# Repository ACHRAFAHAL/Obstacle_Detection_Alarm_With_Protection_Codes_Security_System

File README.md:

# Obstacle Detection Alarm Secured by Protection Codes

## Description

This project outlines the design and implementation of an obstacle detection system that triggers a frequency-modulated audible alarm upon detecting a disrupted red LASER beam. The alarm's deactivation is secured through a precise sequence of three hexadecimal codes, complemented by a rescue code for single errors and a super-code for multiple erroneous entries. This system is ideally suited for various security, surveillance, or access control applications where the detection of unauthorized presence or intrusion is paramount.

## Table of Contents

- [Features](#features)
- [Required Hardware](#required-hardware)
- [Schematics](#schematics)
- [Installation](#installation)
- [Usage](#usage)
- [Contributing](#contributing)

## Features

- **Optical Detection**: The system employs a red LASER emitter and a pair of BPX81 phototransistors for precise obstacle detection. During initial testing phases, a push-button can substitute the optical detection for functional verification. The detection logic utilizes a 74LS32 OR gate, which triggers the alarm as soon as either sensor detects a beam interruption. Visual feedback for sensor activation is provided by a green LED. A LM311 comparator then converts the analog output of the OR gate into a binary signal compatible with the microcontroller.

- **Audible Alarm****: The alarm generates a distinctive two-tone binary modulated sound, alternating between 2500 Hz and 5000 Hz every 0.5 seconds. The core of the sound generation is the XR2206 integrated circuit, configured as a voltage-controlled oscillator (VCO), capable of generating a clean sinusoidal signal. The signal processing chain involves integrating the microcontroller's square wave output into a triangular signal (0-3V) suitable for the XR2206's VCO input, followed by amplification via a push-pull stage to drive the KSSG1708 loudspeaker.

- **Security** Sequence: Alarm deactivation is protected by a precise three-code hexadecimal sequence (Code 1, Code 2, Code 3). In case of an incorrect entry, a "DEFAUT" rescue code (Code 4) can be used for a restricted unlock. For multiple errors, an "ERREUR" super-code (Code 5) is required to fully reset the system procedure. This sequential logic is managed by a state machine implemented in the microcontroller's firmware.

- **Visual Indicators**: The system provides clear visual feedback through three LEDs: a green LED indicates a correct procedure in progress (States 1, 2, and 3). An orange LED signifies the "DEFAUT" state, while a red LED illuminates for the "ERREUR" state. These LEDs are directly driven by the microcontroller.

- **Microcontroller**: The STM32L476RG microcontroller (Nucleo-L476RG development board) serves as the central processing unit, handling the sequential and combinational logic for code verification, error state management (DEFAUT, ERREUR), and memory for predefined codes. It interfaces with a rotary encoder for user input  and an OLED-SSD1306 display for detailed system status and code entry prompts. The microcontroller's internal peripherals, such as timers (TIM2 for encoder, TIM4 for PWM siren ) and external interrupts (EXTI for encoder button ), ensure real-time and reactive system operation.

## Required Hardware

- **LASER emitter**: ADL-65075TL (not explicitly mentioned as a specific component but implied by "red LASER beam" ).
  
- **Phototransistor**: BPX81.
  
- **Operational amplifiers**: TL082  (used in the audio signal chain ).
  
- **Comparator**: LM311.
  
- **Logic Gate**: 74LS32 (OR gate).
  
- **Timer**: While a NE555 is listed in the example, the STM32L476RG's internal timers (TIM2, TIM4) are primarily used for encoder interface  and PWM siren generation  in the project.
  
- **Function generator**: XR2206.
  
- **Mini speaker**: KSSG1708.
  
- **DC-DC Converter**:
IA1215S (for ±15V symmetric power to the audio circuit).
Wurth 173010542 (12V to 5V conversion for the control part).

- **LDO Regulator**: AZ1117CH2-3.3TRG1 (SOT-223 package, for 5V to 3.3V regulation).

- **Development board**: STM32L476RG (Nucleo-L476RG).

- **LEDs**:
Red LEDs (0603 SMD): Quantity: 4 (for power control  and error indication ).
Yellow LED (0603 SMD): Quantity: 1 (for DEFAUT state indication).
Green LED (0603 SMD): Quantity: 1 (for correct procedure indication).

- **Resistors**: Various values (e.g., 220Ω, 400Ω, 800Ω, 1kΩ, 1.6kΩ, 5.1kΩ, 820Ω, 10kΩ, 15kΩ, 3.3kΩ ).
  
- **User inputs**: Rotary encoder (Incrémental MEC (482016514001)) with integrated push-button.

- **Display**: OLED-SSD1306 (I2C interfaced, SBC-OLED01 model).

- **Capacitors**: A range of ceramic (10nF, 100nF ) and electrolytic (1µF, 10µF, 22µF, 47µF, 100µF ) capacitors for filtering, decoupling, and signal coupling.

- **Connectors**: JST connectors (Conn_01x02, Conn_01x03, Conn_01x04 ) for inter-module connections and power input.

- **Protection Diodes**: ESD diodes (WE 82402374) for protecting I2C and encoder lines from electrostatic discharge.

- **Potentiometers**: 20KΩ, 50KΩ, 500Ω  for fine-tuning.

## Schematics

1. **System General Diagram**  
   
   A comprehensive block diagram illustrating the interconnections between the main functional modules: Supply (providing +12V, +5V, +3.3V), NUCLEO-L476RG microcontroller, Rotary Encoder, and Input/Output signals (VALID_ALARM, SIG_ALARM, INPUT, INPUT_Supply). It also shows the I2C connection to the OLED-SSD1306 display  and the mounting holes for the PCB.
   
3. **Sensor Model**  
   
   This schematic details the obstacle detection unit. It includes two BPX81 phototransistors (Q1, Q2)  that detect the interruption of the LASER beam. Their outputs feed into a 74LS32 OR gate (U1), which activates when either beam is broken. A verification LED (D3, GREEN_LED)  provides visual confirmation of sensor activation. The signal is then passed to an LM311 comparator (U2), which compares the OR gate's output to a 2.5V reference voltage, producing a binary signal for the microcontroller. This section also includes power supply filtering and visual indicators using NPN (2N1711) and PNP (2N2905) transistors.
   
5. **Audio Signal Chain**  
   
   This diagram illustrates the steps involved in generating and amplifying the alarm sound. The process begins with a square wave signal (0 to 3.3V) from the microcontroller (STM32). This signal is then integrated by an operational amplifier (U1A) to transform it into a triangular wave centered at 0V (±1.65V). A second operational amplifier (U1B), configured as a non-inverting amplifier, shifts and scales this signal to a 0-3V range, suitable for the XR2206's VCO input. The XR2206 (U2) then generates the frequency-modulated sinusoidal signal (2500 Hz / 5000 Hz). Finally, this signal is amplified by a symmetric push-pull stage using 2N1711 (Q1) and 2N2905 (Q2) transistors  to drive the KSSG1708 loudspeaker (LS1). The audio circuit is powered by a ±15V symmetric supply generated by an IA1215S DC-DC converter (PS1) from a 12V input.
   
7. **Unlock Sequence**  
   
   This state graph (Figure 1.1) visually represents the precise sequential logic for alarm deactivation. Starting from the "ALARME INACTIVE" (Etat 0) state, an active sensor transitions the system to "ALARME ACTIVE" (Etat 1). The user must then enter three correct codes sequentially (Code 1, Code 2, Code 3), moving through Etat 1, Etat 2, and Etat 3. If any code is incorrect, the system branches to a "DEFAUT" state (Etat 4), requiring Code 4. If Code 4 is incorrect, or multiple errors occur, it transitions to an "ERREUR" state (Etat 5), requiring Code 5 to reset the system. A successful sequence at Etat 3 returns the system to "ALARME INACTIVE" (Etat 0).

## Installation

**PCB Fabrication**: Generate Gerber files from the KiCad projects for each of the three main parts: Detection, Control, and Actuator. These files are then sent to a PCB manufacturer.

**Component Soldering**: Upon receiving the engraved PCBs, manually solder all through-hole components. Special attention should be paid to the spacing and quality of solder joints to prevent issues like short-circuits, as encountered during initial testing.

**Power Supply Integration**: For the Control PCB, integrate the J401 connector for the 12V input, the Wurth 173010542 DC-DC converter (U401) for 12V to 5V conversion, and the AZ1117CH2-3.3TRG1 LDO regulator (U402) for 5V to 3.3V regulation. Visual control LEDs (D401, D402, D403) should be verified for proper operation.

**Microcontroller Setup**: Carefully mount the Nucleo-L476RG board onto the designated footprint on the Control PCB.
Interconnections: Connect the Detection module to the Control module via J1 and J3 connectors. Ensure proper signal connections for INPUT (laser detection)  and INPUT_Supply. Connect the Control module to the Actuator module via the J2 connector, ensuring correct routing for VALID_ALARM (alarm activation signal)  and SIG_ALARM (power supply to the output circuit).

**Firmware**: Program the STM32L476RG microcontroller with the project firmware. The software is designed with a modular architecture, leveraging the microcontroller's internal peripherals such as timers (TIM2 for encoder, TIM4 for PWM siren ), external interrupts (EXTI for encoder button press ), I2C for OLED communication, and GPIOs for LED control. This ensures efficient and responsive operation.

## Usage
**System Activation**: The alarm system is initialized in an "ALARM INACTIVE" (Etat 0) state, as shown on the OLED display.
Obstacle Detection: When an obstacle interrupts the LASER beam, the phototransistors detect the change, triggering the 74LS32 OR gate  and the LM311 comparator. This sends a logical front signal to the STM32's INPUT pin, transitioning the system to the "ALARM ACTIVE" state (Etat 1). The audible alarm will simultaneously be triggered.

**Alarm Deactivation**: To disarm the alarm, the user must enter a sequence of three correct hexadecimal codes (Code 1, Code 2, Code 3) using the rotary encoder. 
Code Entry: Rotate the encoder to select a character (0 to F)  and press the integrated push-button to validate each character. The OLED display will guide the user by showing prompts like "CODE 1:X", "CODE D:X", or "CODE E:X".

**Correct Sequence**: Successful entry of Code 1, Code 2, and Code 3 (transitioning through Etat 1, Etat 2, and Etat 3)  will deactivate the alarm, and the system will revert to the "ALARM OFF" state (Etat 0). The green LED will illuminate during the correct procedure.

Incorrect Entry (DEFAUT State): If a code is entered incorrectly, the system may transition to the "DEFAUT" state (Etat 4), requiring the user to enter a specific rescue code (Code 4). The orange LED will indicate this state.

Multiple Errors (ERREUR State): In cases of multiple incorrect entries or an incorrect rescue code, the system will enter the "ERREUR" state (Etat 5), demanding the entry of a super-code (Code 5)  to reset the entire procedure and return to Etat 0. The red LED will blink to signify this critical error state.

**Visual Feedback**: The OLED display provides real-time information on the system's status and the progress of code entry. The three colored LEDs (Green, Orange, Red) offer immediate visual cues regarding the system's current state and the validity of code entries.

## contributing

<br>

<table align="center">
  <tr>
    <td align="center">
      <br />
      <sub><b>Ahal Achraf</b></sub><br />
      <small>Control Part</small><br />
      <a href="https://github.com/ACHRAFAHAL">GitHub</a>
    </td>
  </tr>
  <tr>
    <td align="center">
      <br />
      <sub><b>Hussain Ali</b></sub><br />
      <small>Control Part</small><br />
      <a href="https://github.com/H-Ali-92">GitHub</a>
   </td>
  </tr>
</table>
<br>

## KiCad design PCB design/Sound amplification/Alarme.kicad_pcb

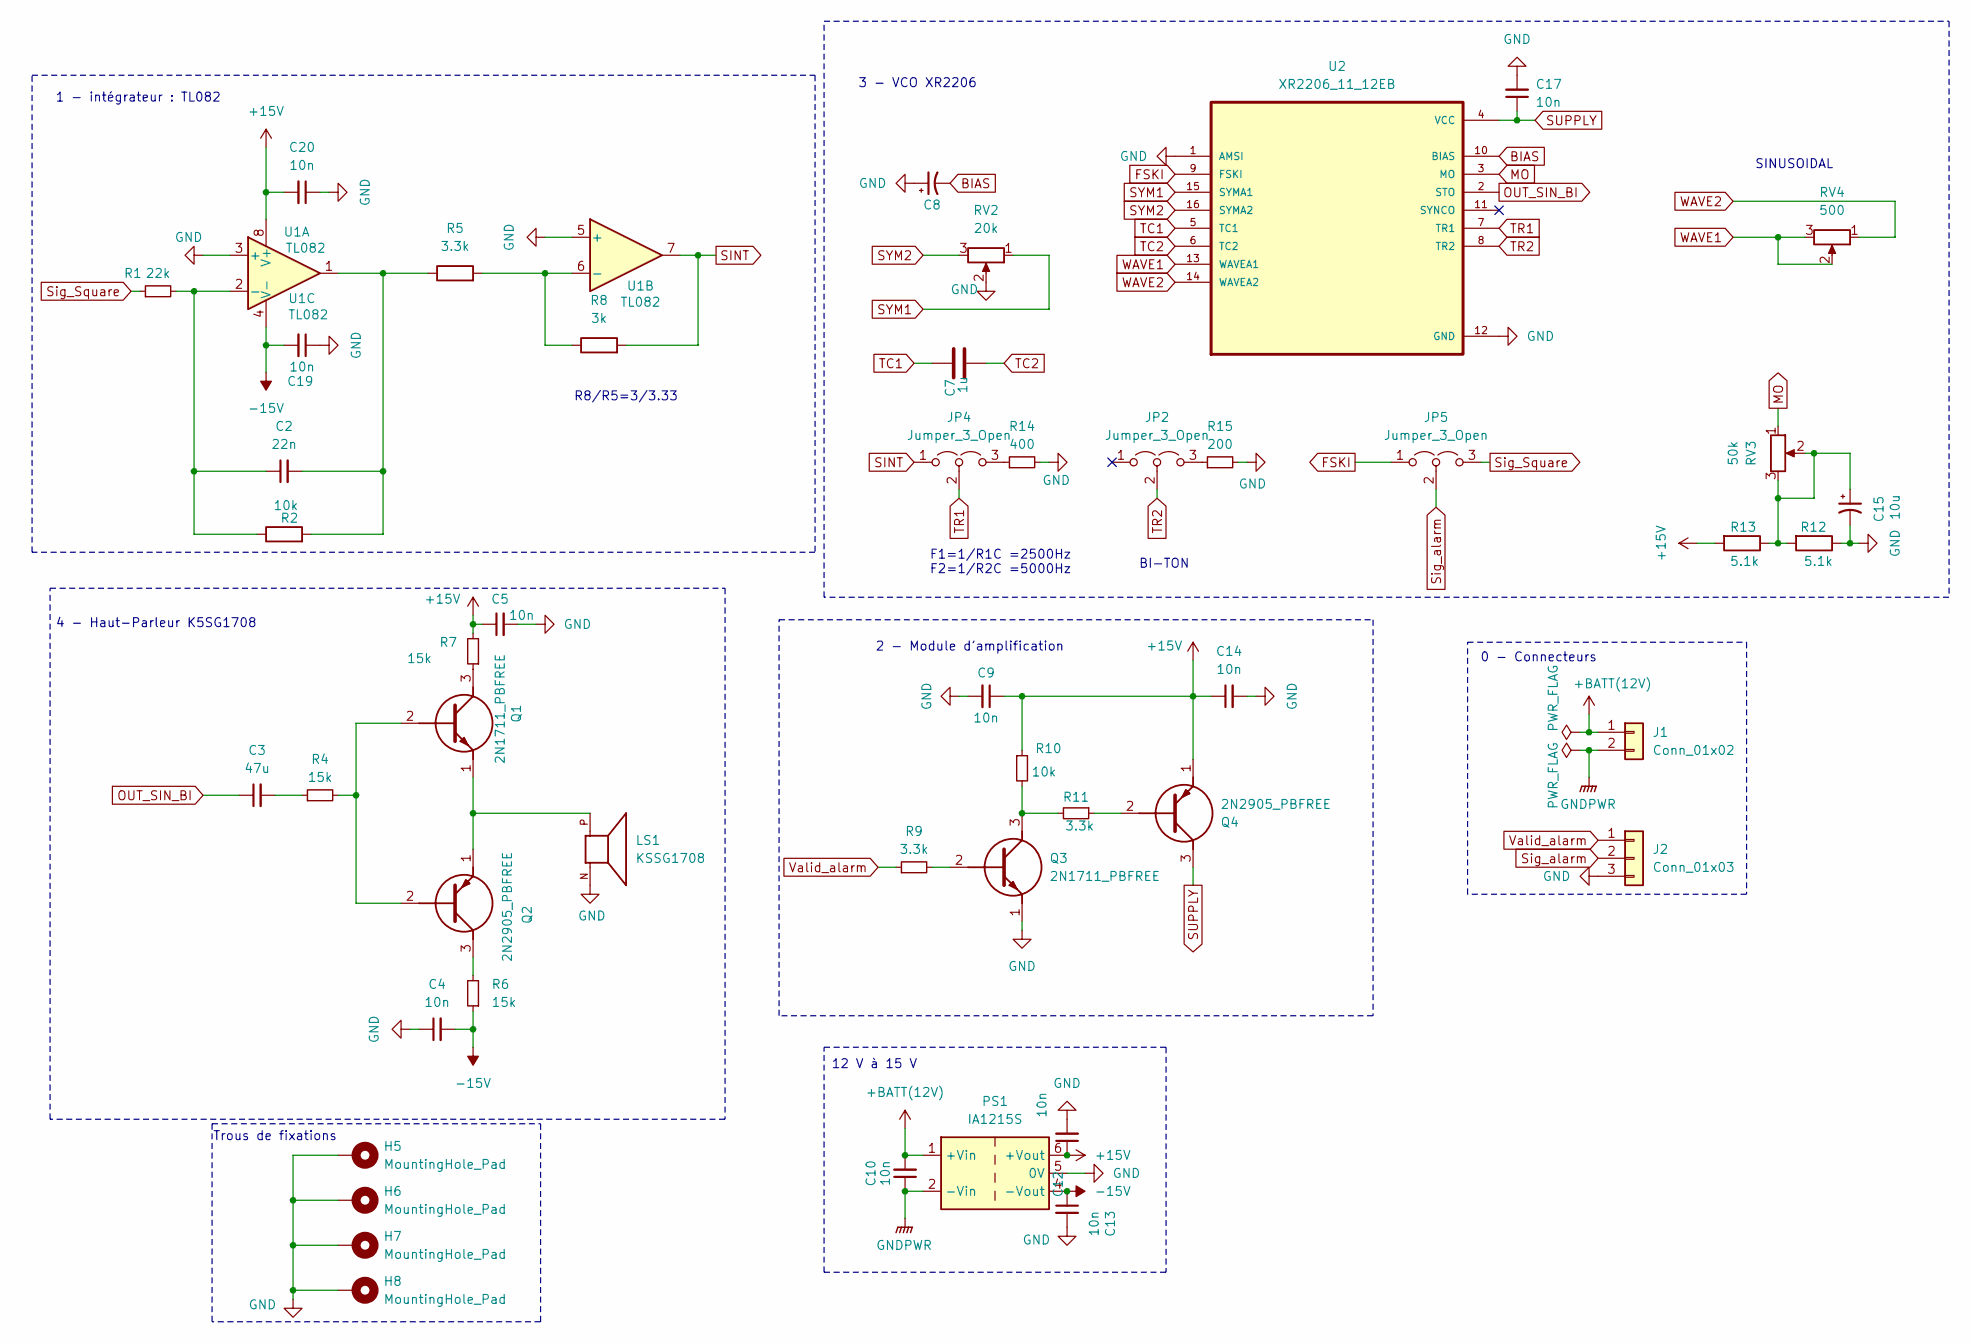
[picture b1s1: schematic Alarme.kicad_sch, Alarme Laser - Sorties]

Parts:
C2: 22n; CP_Radial_Tantal_D4.5mm_P5.00mm
C3: 47u; CP_Radial_Tantal_D4.5mm_P5.00mm
C4, C5, C8, C9, C10, C12, C13, C14, C17, C19, C20: 10n; CP_Radial_Tantal_D4.5mm_P5.00mm
C7: 1u; CP_Radial_Tantal_D4.5mm_P5.00mm
C15: 10u; CP_Radial_Tantal_D4.5mm_P5.00mm
H5, H6, H7, H8: MountingHole_Pad; MountingHole_3.2mm_M3_DIN965_Pad
J1: Conn_01x02; JST_XH_B2B-XH-A_1x02_P2.50mm_Vertical
J2: Conn_01x03; JST_XH_B3B-XH-A_1x03_P2.50mm_Vertical
JP2, JP4, JP5: Jumper_3_Open; PinHeader_1x03_P2.54mm_Vertical
LS1: KSSG1708; SPKR_KSSG1708; PARTREV 1.1
PS1: IA1215S; Converter_DCDC_XP_POWER-IAxxxxS_THT
Q1, Q3: 2N1711_PBFREE; TO39; Mouser Part Number 610-2N1711
Q2, Q4: 2N2905_PBFREE; TO39; Mouser Part Number 610-2N2905
R1: 22k; R_Axial_DIN0204_L3.6mm_D1.6mm_P2.54mm_Vertical
R2, R10: 10k; R_Axial_DIN0204_L3.6mm_D1.6mm_P2.54mm_Vertical
R4, R6, R7: 15k; R_Axial_DIN0204_L3.6mm_D1.6mm_P2.54mm_Vertical
R5, R9, R11: 3.3k; R_Axial_DIN0204_L3.6mm_D1.6mm_P2.54mm_Vertical
R8: 3k; R_Axial_DIN0204_L3.6mm_D1.6mm_P2.54mm_Vertical
R12, R13: 5.1k; R_Axial_DIN0204_L3.6mm_D1.6mm_P2.54mm_Vertical
R14: 400; R_Axial_DIN0204_L3.6mm_D1.6mm_P2.54mm_Vertical
R15: 200; R_Axial_DIN0204_L3.6mm_D1.6mm_P2.54mm_Vertical
RV2: 20k; Potentiometer_ACP_CA9-H5_Horizontal
RV3: 50k; Potentiometer_ACP_CA9-H5_Horizontal
RV4: 500; Potentiometer_ACP_CA9-H5_Horizontal
U1: TL082; DIP794W53P254L959H508Q8N
U2: XR2206_11_12EB; DIP-16_W7.62mm_LongPads; PART_REV 1.03; DIGI-KEY_PART_NUMBER 1016-1428-ND

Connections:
+15V: C5.1, C9.1, C12.1, C14.1, C20.2, PS1.6 (+Vout), Q4.1 (E), R7.2, R10.1, R13.2, U1.8 (V+)
+BATT(12V): C10.2, J1.1, PS1.1 (+Vin)
-15V: C4.2, C13.1, C19.2, PS1.4 (-Vout), R6.1, U1.4 (V-)
BIAS: C8.2, U2.10 (BIAS)
FSKI: JP5.1 (A), U2.9 (FSKI)
GND: C4.1, C5.2, C8.1, C9.2, C12.2, C13.2, C14.2, C15.2, C17.2, C19.1, C20.1, H5.1, H6.1, H7.1, H8.1, J2.3, LS1.N, PS1.5 (0V), Q3.1 (E), R12.1, R14.2, R15.2, RV2.2, U1.3 (+), U1.5 (+), U2.1 (AMSI), U2.12 (GND)
GNDPWR: C10.1, J1.2, PS1.2 (-Vin)
MO: RV3.1, U2.3 (MO)
unnamed: C2.2, R2.2, R5.1, U1.1
unnamed: C3.2, R4.1
unnamed: C15.1, R12.2, R13.1, RV3.2, RV3.3
unnamed: JP2.3 (B), R15.1
unnamed: JP4.3 (B), R14.1
unnamed: Q1.2 (B), Q2.2 (B), R4.2
unnamed: Q1.3 (C), R7.1
unnamed: LS1.P, Q1.1 (E), Q2.1 (E)
unnamed: Q2.3 (C), R6.2
unnamed: Q3.2 (B), R9.2
unnamed: Q3.3 (C), R10.2, R11.2
unnamed: Q4.2 (B), R11.1
unnamed: C2.1, R1.2, R2.1, U1.2 (-)
unnamed: R5.2, R8.1, U1.6 (-)
OUT_SIN_BI: C3.1, U2.2 (STO)
SINT: JP4.1 (A), R8.2, U1.7
SUPPLY: C17.1, Q4.3 (C), U2.4 (VCC)
SYM1: RV2.1, U2.15 (SYMA1)
SYM2: RV2.3, U2.16 (SYMA2)
Sig_Square: JP5.3 (B), R1.1
Sig_alarm: J2.2, JP5.2 (C)
TC1: C7.1, U2.5 (TC1)
TC2: C7.2, U2.6 (TC2)
TR1: JP4.2 (C), U2.7 (TR1)
TR2: JP2.2 (C), U2.8 (TR2)
Valid_alarm: J2.1, R9.1
WAVE1: RV4.2, RV4.3, U2.13 (WAVEA1)
WAVE2: RV4.1, U2.14 (WAVEA2)

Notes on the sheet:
BI-TON
R8/R5=3/3.33
F1=1/R1C =2500Hz F2=1/R2C =5000Hz
SINUSOIDAL
3 - VCO XR2206
1 - intégrateur : TL082
0 - Connecteurs
Trous de fixations
4 - Haut-Parleur K5SG1708
2 - Module d'amplification
12 V à 15 V

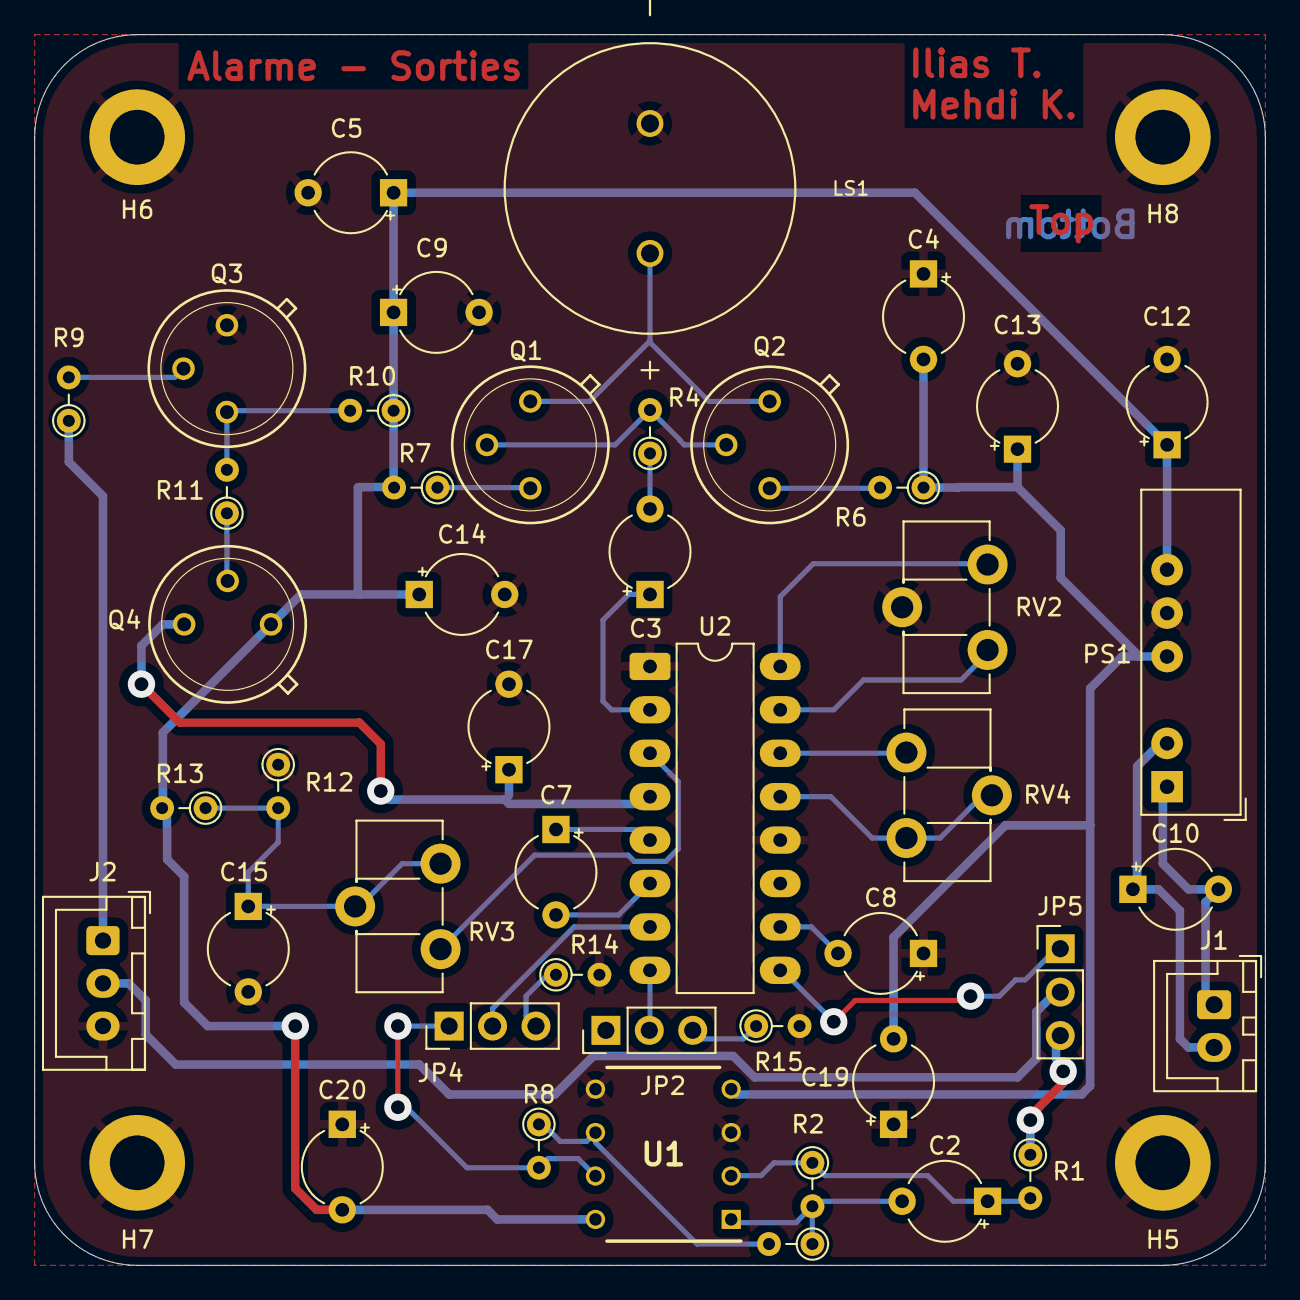
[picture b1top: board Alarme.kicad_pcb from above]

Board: 2 copper layers, 72.0 x 72.0 mm, 49 parts (0 on the bottom side), 36 nets.

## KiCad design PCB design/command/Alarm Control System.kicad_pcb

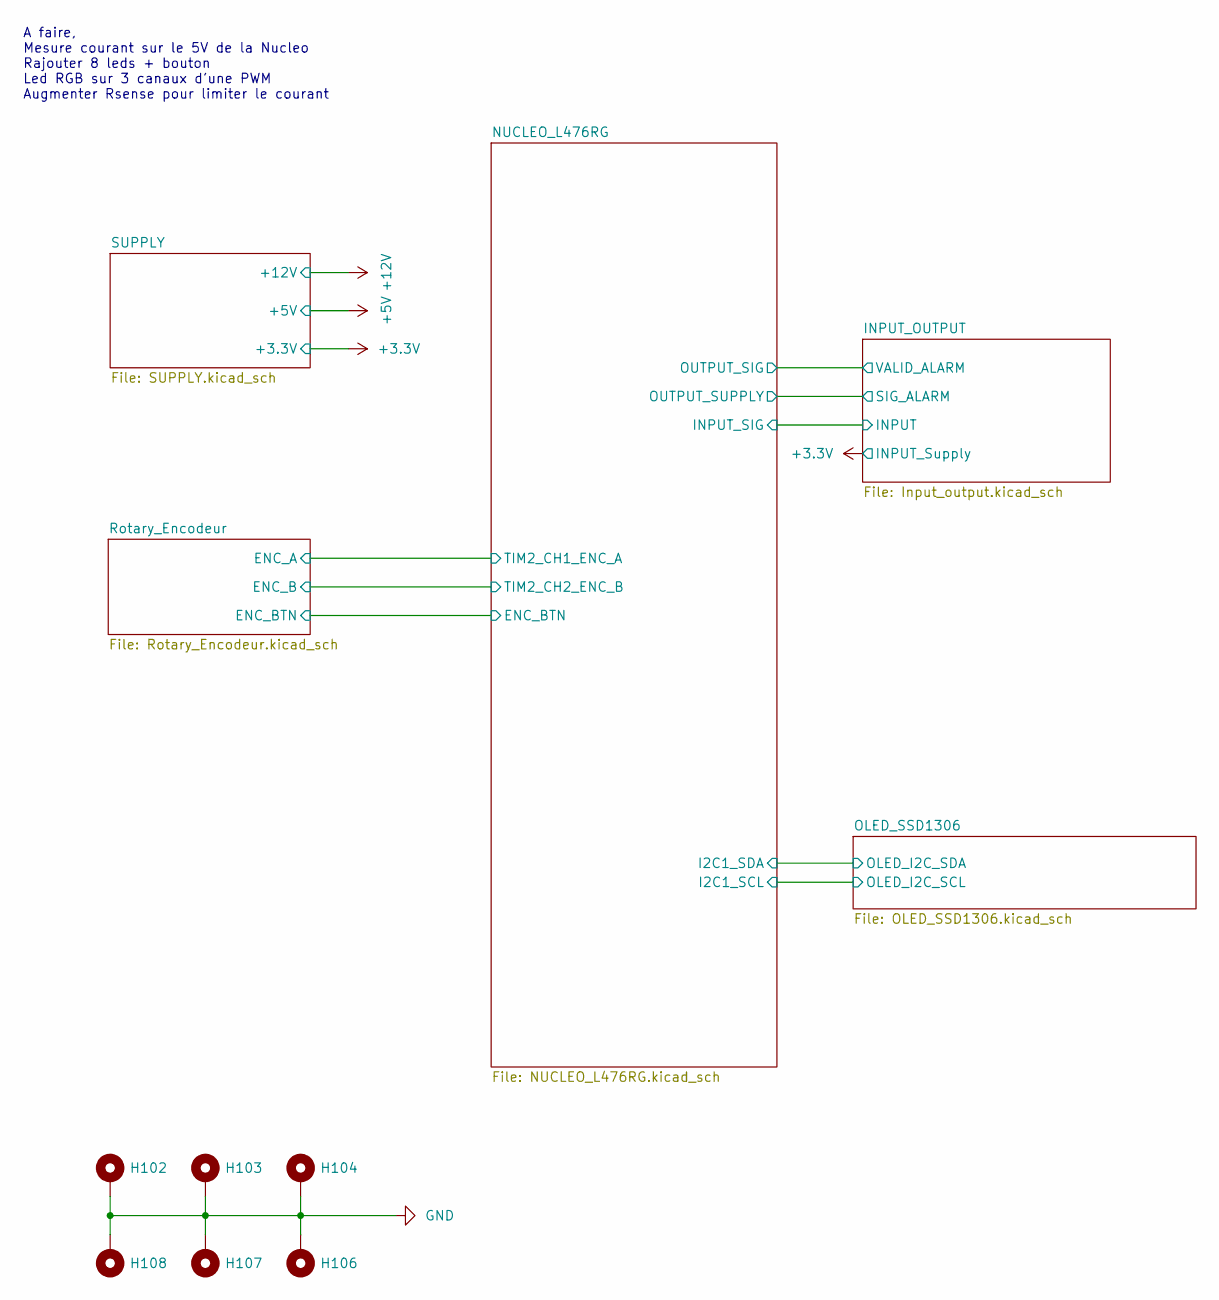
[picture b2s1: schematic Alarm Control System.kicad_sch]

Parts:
H102, H103, H104, H106, H107, H108: MountingHole_Pad; MountingHole_3.2mm_M3_Pad

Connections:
GND: H102.1, H103.1, H104.1, H106.1, H107.1, H108.1; also elsewhere on the board

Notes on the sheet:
A faire, Mesure courant sur le 5V de la Nucleo Rajouter 8 leds + bouton Led RGB sur 3 canaux d'une PWM Augmenter Rsense pour limiter le courant

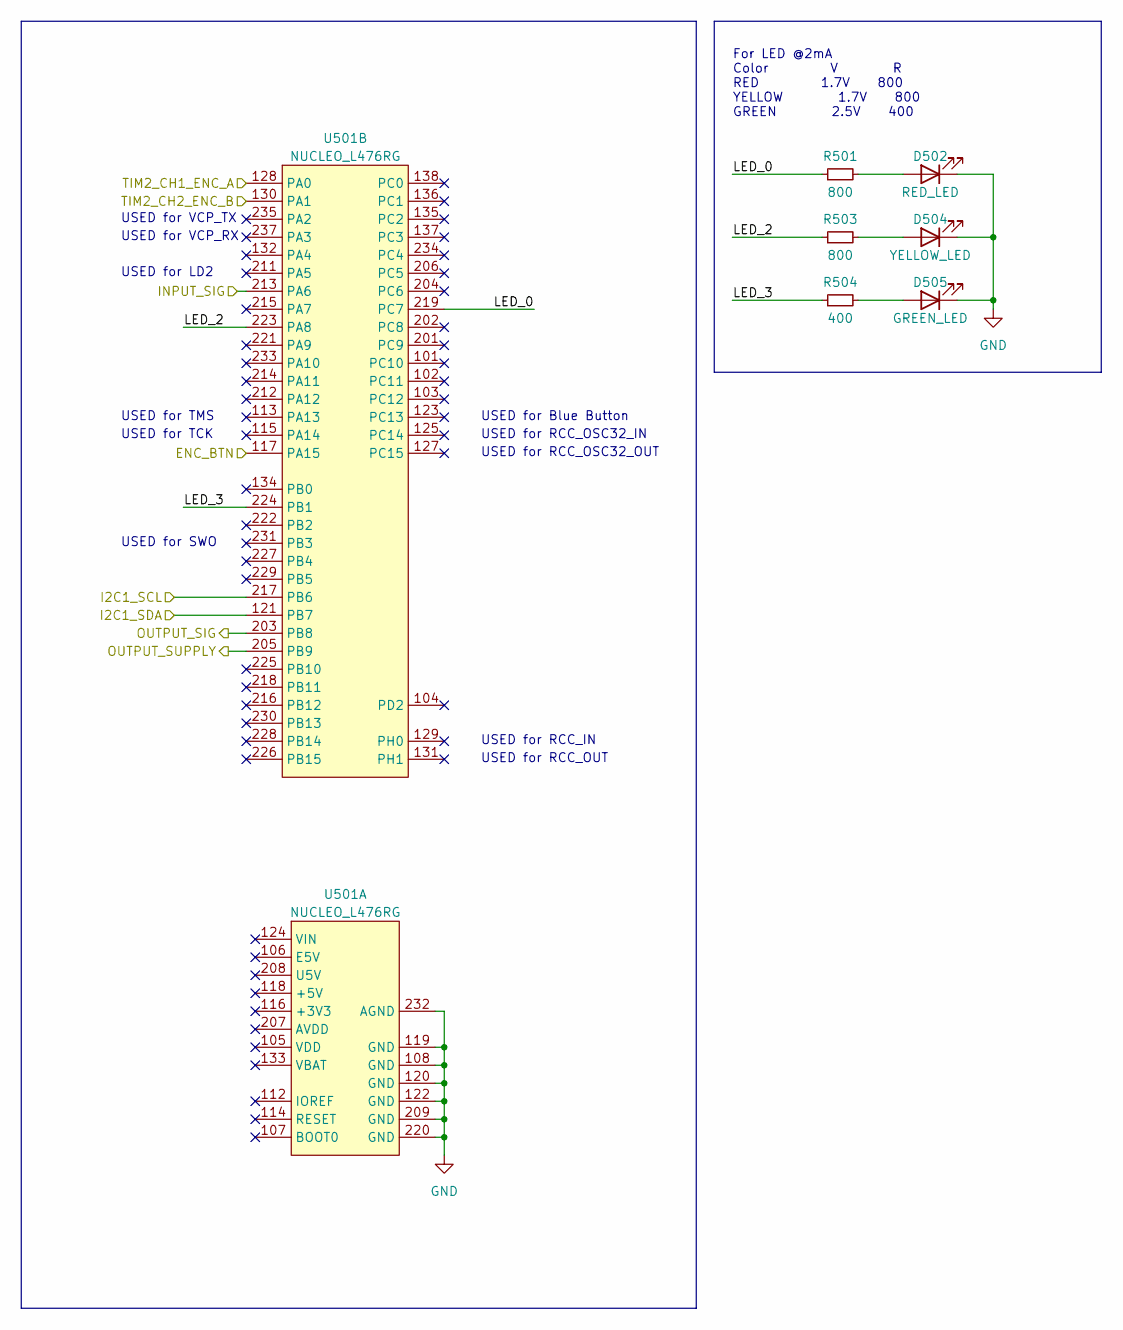
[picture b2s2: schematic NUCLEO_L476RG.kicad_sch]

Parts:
D502: RED_LED; LED_0603_1608Metric; MPN WE 150060RS55040
D504: YELLOW_LED; LED_0603_1608Metric; MPN WE 150060YS55040
D505: GREEN_LED; LED_0603_1608Metric; MPN WE 150060GS55040
R501, R503: 800; R_0402_1005Metric
R504: 400; R_0402_1005Metric
U501: NUCLEO_L476RG; MPN TSW-119-19-T-D

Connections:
/INPUT_OUTPUT/INPUT: U501.213 (PA6); also elsewhere on the board
/INPUT_OUTPUT/SIG_ALARM: U501.205 (PB9); also elsewhere on the board
/INPUT_OUTPUT/VALID_ALARM: U501.203 (PB8); also elsewhere on the board
/NUCLEO_L476RG/ENC_BTN: U501.117 (PA15); also elsewhere on the board
/NUCLEO_L476RG/I2C1_SCL: U501.217 (PB6); also elsewhere on the board
/NUCLEO_L476RG/I2C1_SDA: U501.121 (PB7); also elsewhere on the board
/NUCLEO_L476RG/LED_0: R501.1, U501.219 (PC7)
/NUCLEO_L476RG/LED_2: R503.1, U501.223 (PA8)
/NUCLEO_L476RG/LED_3: R504.1, U501.224 (PB1)
/NUCLEO_L476RG/TIM2_CH1_ENC_A: U501.128 (PA0); also elsewhere on the board
/NUCLEO_L476RG/TIM2_CH2_ENC_B: U501.130 (PA1); also elsewhere on the board
GND: D502.1 (K), D504.1 (K), D505.1 (K), U501.108 (GND), U501.119 (GND), U501.120 (GND), U501.122 (GND), U501.209 (GND), U501.220 (GND), U501.232 (AGND); also elsewhere on the board
unnamed: D502.2 (A), R501.2
unnamed: D504.2 (A), R503.2
unnamed: D505.2 (A), R504.2

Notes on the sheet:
USED for SWO
USED for RCC_OUT
USED for VCP_RX
USED for RCC_OSC32_IN
USED for Blue Button
USED for RCC_IN
USED for RCC_OSC32_OUT
For LED @2mA Color V R RED 1.7V 800 YELLOW 1.7V 800 GREEN 2.5V 400
USED for TMS
USED for TCK
USED for VCP_TX
USED for LD2

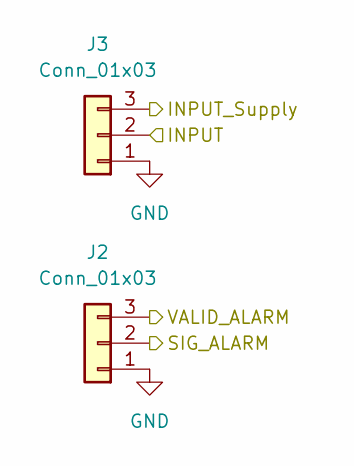
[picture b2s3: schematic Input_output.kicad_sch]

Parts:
J2, J3: Conn_01x03; JST_EH_S3B-EH_1x03_P2.50mm_Horizontal

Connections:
+3.3V: J3.3; also elsewhere on the board
/INPUT_OUTPUT/INPUT: J3.2; also elsewhere on the board
/INPUT_OUTPUT/SIG_ALARM: J2.2; also elsewhere on the board
/INPUT_OUTPUT/VALID_ALARM: J2.3; also elsewhere on the board
GND: J2.1, J3.1; also elsewhere on the board

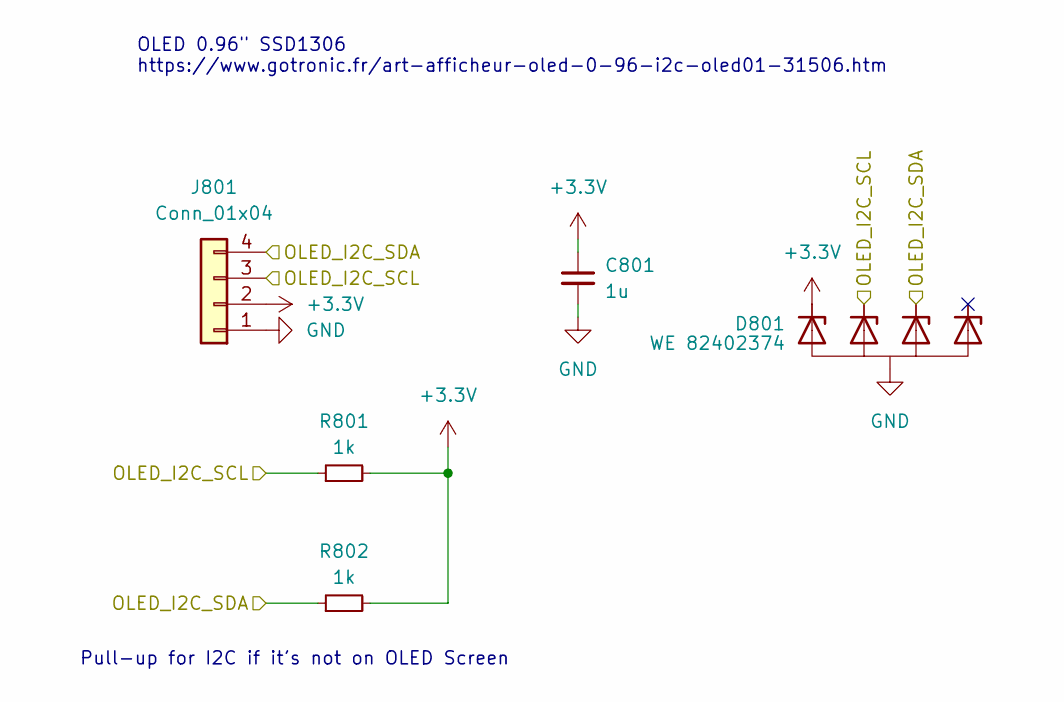
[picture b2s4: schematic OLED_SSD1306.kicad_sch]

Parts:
C801: 1u; C_0402_1005Metric
D801: WE 82402374; SC70-5L; MPN WE 82402374
J801: Conn_01x04; SBC-OLED01
R801, R802: 1k; R_0402_1005Metric

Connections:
+3.3V: C801.1, D801.5 (I/O), J801.2, R801.2, R802.2; also elsewhere on the board
/NUCLEO_L476RG/I2C1_SCL: D801.4 (I/O), J801.3, R801.1; also elsewhere on the board
/NUCLEO_L476RG/I2C1_SDA: D801.3 (I/O), J801.4, R802.1; also elsewhere on the board
GND: C801.2, D801.2 (GND), J801.1; also elsewhere on the board

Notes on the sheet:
OLED 0.96" SSD1306 https://www.gotronic.fr/art-afficheur-oled-0-96-i2c-oled01-31506.htm
Pull-up for I2C if it's not on OLED Screen

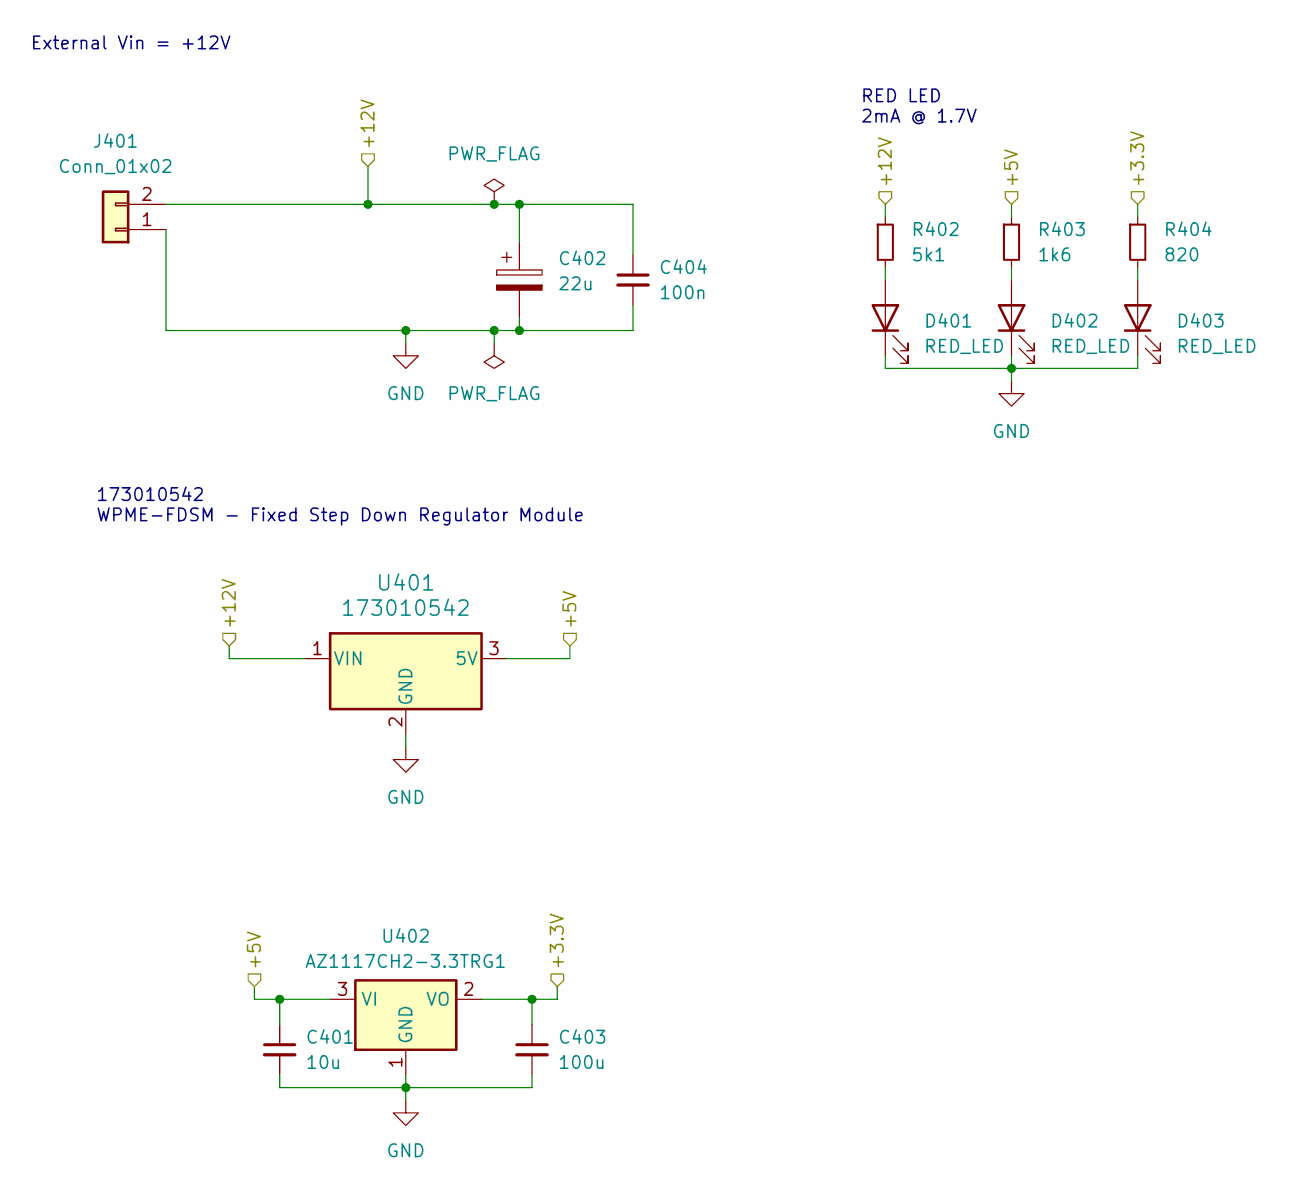
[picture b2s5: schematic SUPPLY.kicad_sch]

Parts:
C401: 10u; C_0402_1005Metric
C402: 22u; CP_Elec_5x5.4; MPN 865060442002
C403: 100u; C_0402_1005Metric
C404: 100n; C_0402_1005Metric
D401, D402, D403: RED_LED; LED_0603_1608Metric; MPN WE 150060RS55040
J401: Conn_01x02; JST_XH_S2B-XH-A_1x02_P2.50mm_Horizontal
R402: 5k1; R_0402_1005Metric
R403: 1k6; R_0402_1005Metric
R404: 820; R_0402_1005Metric
U401: 173010542; 173010xxx
U402: AZ1117CH2-3.3TRG1; SOT-223-3_TabPin2; MPN AZ1117CH2-3.3TRG1

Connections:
+3.3V: C403.1, R404.1, U402.2 (VO); also elsewhere on the board
+5V: C401.1, R403.1, U401.3 (5V), U402.3 (VI)
+12V: C402.1, C404.1, J401.2, R402.1, U401.1 (VIN)
GND: C401.2, C402.2, C403.2, C404.2, D401.1 (K), D402.1 (K), D403.1 (K), J401.1, U401.2 (GND), U402.1 (GND); also elsewhere on the board
unnamed: D401.2 (A), R402.2
unnamed: D402.2 (A), R403.2
unnamed: D403.2 (A), R404.2

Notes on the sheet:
RED LED 2mA @ 1.7V
173010542 WPME-FDSM - Fixed Step Down Regulator Module
External Vin = +12V

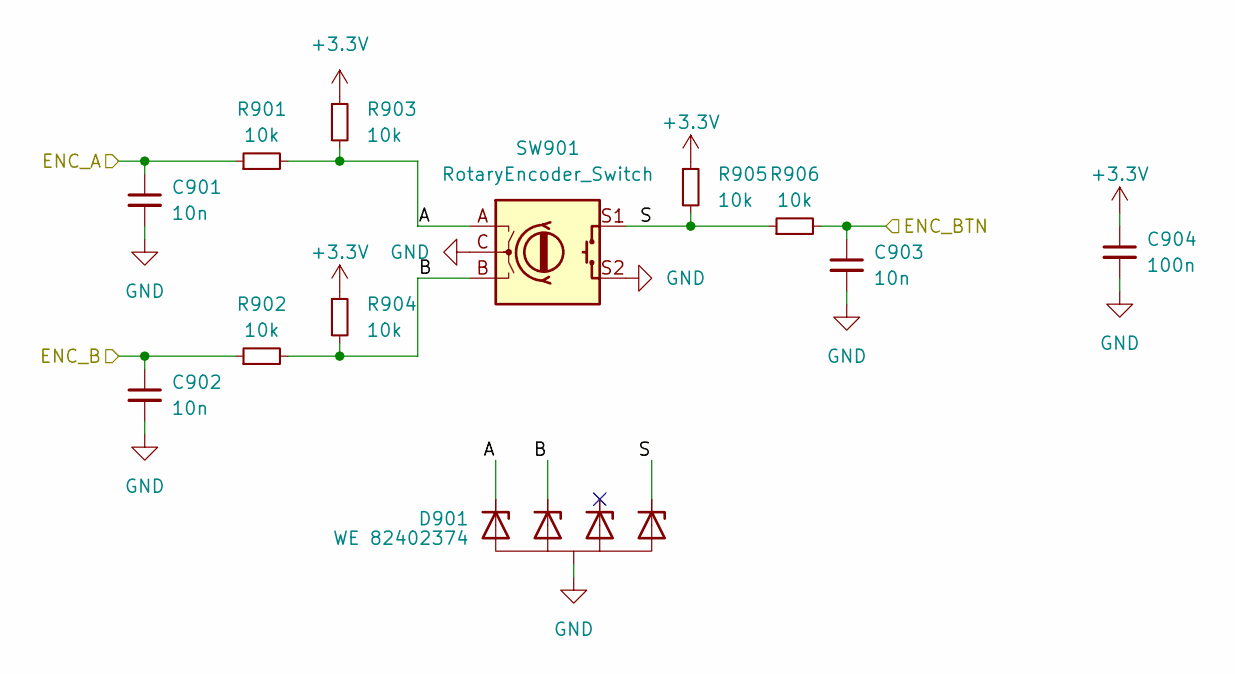
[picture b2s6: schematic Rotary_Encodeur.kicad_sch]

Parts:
C901, C902, C903: 10n; C_0402_1005Metric
C904: 100n; C_0402_1005Metric
D901: WE 82402374; SC70-5L; MPN WE 82402374
R901, R902, R903, R904, R905, R906: 10k; R_0402_1005Metric
SW901: RotaryEncoder_Switch; 482016514001_Mechanical_Incremental_Encoder_Switch; MPN WE 482016514001

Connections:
+3.3V: C904.1, R903.1, R904.1, R905.1; also elsewhere on the board
/NUCLEO_L476RG/ENC_BTN: C903.1, R906.2; also elsewhere on the board
/NUCLEO_L476RG/TIM2_CH1_ENC_A: C901.1, R901.1; also elsewhere on the board
/NUCLEO_L476RG/TIM2_CH2_ENC_B: C902.1, R902.1; also elsewhere on the board
/Rotary_Encodeur/A: D901.5 (I/O), R901.2, R903.2, SW901.A
/Rotary_Encodeur/B: D901.4 (I/O), R902.2, R904.2, SW901.B
/Rotary_Encodeur/S: D901.1 (I/O), R905.2, R906.1, SW901.S1
GND: C901.2, C902.2, C903.2, C904.2, D901.2 (GND), SW901.C, SW901.S2; also elsewhere on the board

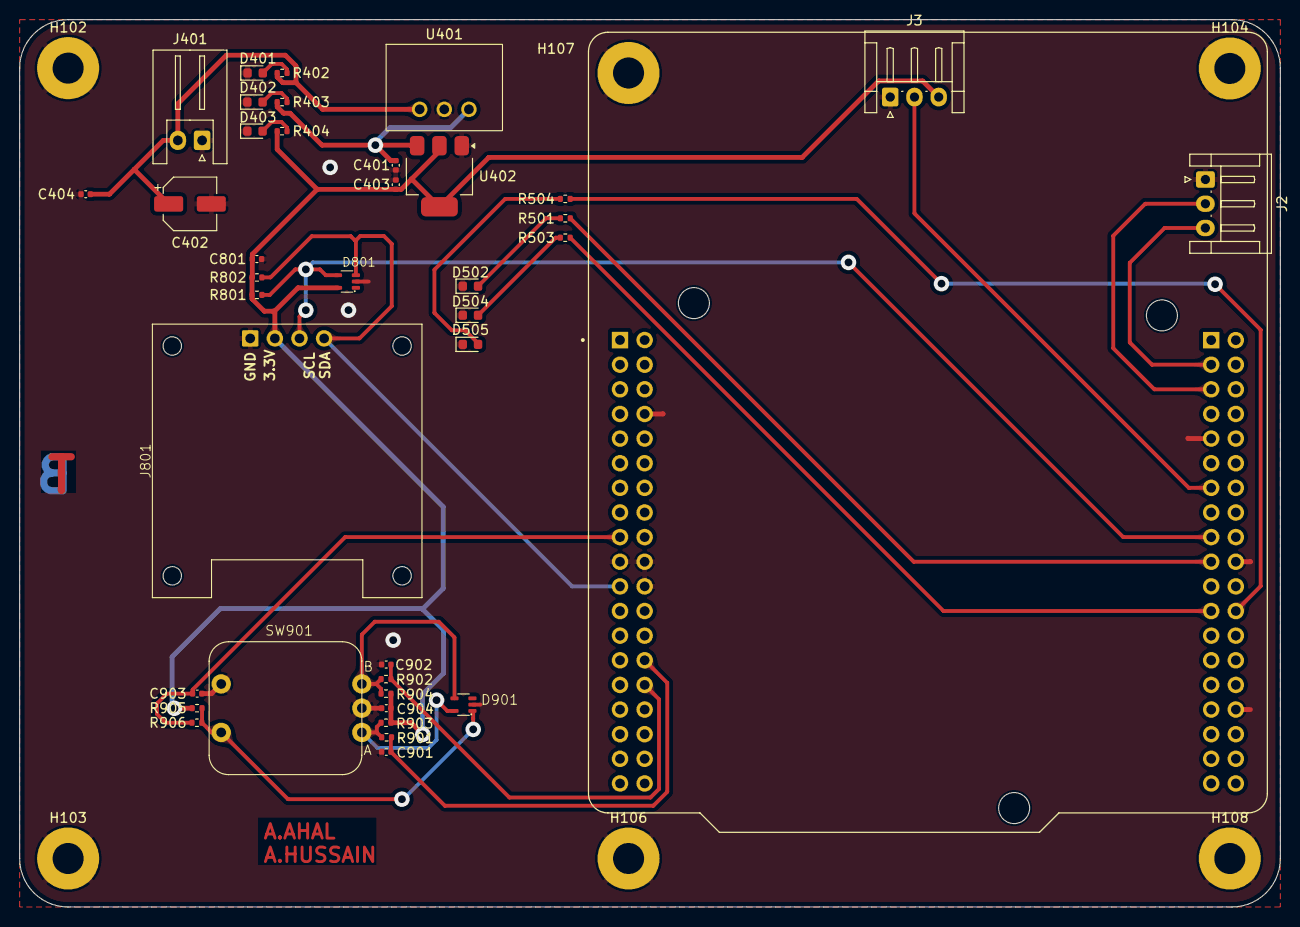
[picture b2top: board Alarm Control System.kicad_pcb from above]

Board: 2 copper layers, 130.0 x 91.5 mm, 45 parts (0 on the bottom side), 24 nets.

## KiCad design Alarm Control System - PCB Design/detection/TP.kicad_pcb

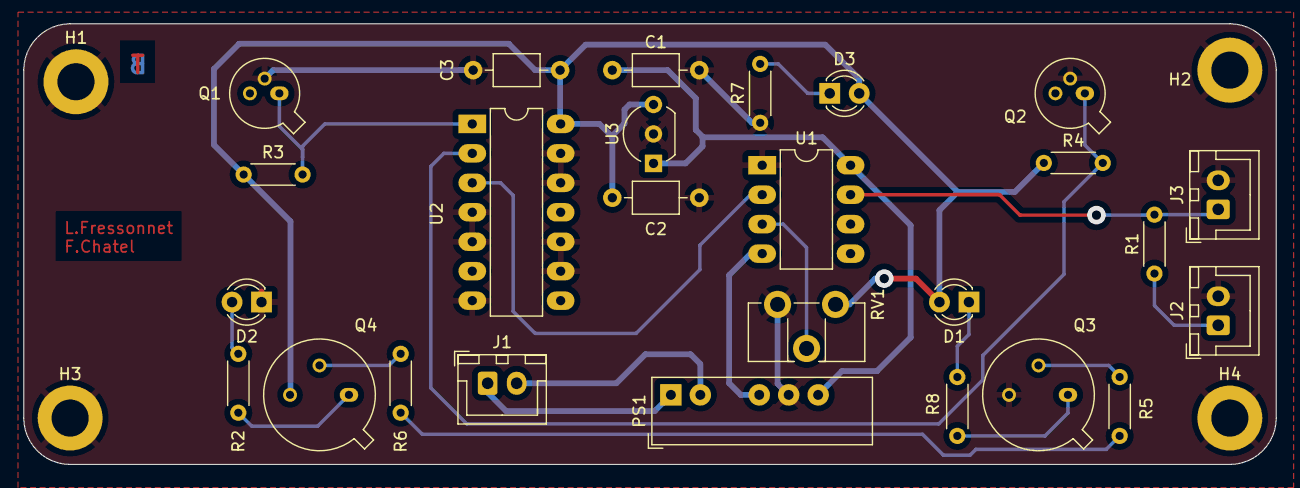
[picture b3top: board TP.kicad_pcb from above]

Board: 2 copper layers, 108.0 x 38.0 mm, 30 parts (0 on the bottom side), 20 nets.

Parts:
C1: 0.33µF; C_Axial_L3.8mm_D2.6mm_P7.50mm_Horizontal
C2: 0.1µF; C_Axial_L3.8mm_D2.6mm_P7.50mm_Horizontal
C3: 10nF; C_Axial_L3.8mm_D2.6mm_P7.50mm_Horizontal
D1, D3: RED_LED; LED_D3.0mm
D2: GREEN_LED; LED_D3.0mm
H1, H2, H3, H4: MountingHole_Pad; MountingHole_3.2mm_M3_DIN965_Pad
J1, J2, J3: Conn_01x02; JST_XH_B2B-XH-A_1x02_P2.50mm_Vertical
PS1: IA1215S; Converter_DCDC_XP_POWER-IAxxxxS_THT
Q1, Q2: Q_Photo_NPN; TO-18-3_Lens
Q3: 2N1711; TO-39-3
Q4: 2N2905; TO-39-3
R1: 660; R_Axial_DIN0204_L3.6mm_D1.6mm_P5.08mm_Horizontal
R2, R8: 220; R_Axial_DIN0204_L3.6mm_D1.6mm_P5.08mm_Horizontal
R3, R4: 1k; R_Axial_DIN0204_L3.6mm_D1.6mm_P5.08mm_Horizontal
R5, R6: 43k; R_Axial_DIN0204_L3.6mm_D1.6mm_P5.08mm_Horizontal
R7: R; R_Axial_DIN0204_L3.6mm_D1.6mm_P5.08mm_Horizontal
RV1: 100K; Potentiometer_ACP_CA9-H3,8_Horizontal
U1: LM311; DIP-8_W7.62mm_LongPads
U2: 74LS32; DIP-14_W7.62mm_LongPads
U3: L7805; TO-92_Inline_Wide

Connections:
74LS32: R5.1, R6.1
74LS32_Out: U1.2 (+), U2.3
+3.3V: J2.1, R1.1
+5V: C2.1, C3.1, D1.2 (A), D3.2 (A), Q4.3 (E), R3.1, R4.1, RV1.1, U2.14 (VCC), U3.3 (OUT)
+12V: J1.1, PS1.1 (+Vin)
+15V: C1.1, PS1.6 (+Vout), U1.8 (V+), U3.1 (IN)
-15V: PS1.4 (-Vout), U1.4 (V-)
Alarme_out: J3.1, R1.2, U1.7
C_Q1: Q1.1 (C), R3.2, U2.1
C_Q2: Q2.1 (C), R4.2, U2.2
GND: C1.2, C2.2, C3.2, D2.1 (K), H1.1, H2.1, H3.1, H4.1, J2.2, J3.2, PS1.5 (0V), Q1.2 (E), Q2.2 (E), Q3.3 (E), R7.1, RV1.3, U1.1 (GND), U2.4, U2.5, U2.7 (GND), U2.9, U2.10, U2.12, U2.13, U3.2 (GND)
GNDPWR: J1.2, PS1.2 (-Vin)
unnamed: D1.1 (K), R8.1
unnamed: D2.2 (A), R2.2
unnamed: D3.1 (K), R7.2
unnamed: Q3.2 (B), R5.2
unnamed: Q3.1 (C), R8.2
unnamed: Q4.2 (B), R6.2
unnamed: Q4.1 (C), R2.1
unnamed: RV1.2, U1.3 (-)

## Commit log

2025-03-10 STM32 code upload
2025-03-10 STM32 code update 2
2025-04-14 PCB added
2025-04-19 update docs
2025-06-05 Create md
